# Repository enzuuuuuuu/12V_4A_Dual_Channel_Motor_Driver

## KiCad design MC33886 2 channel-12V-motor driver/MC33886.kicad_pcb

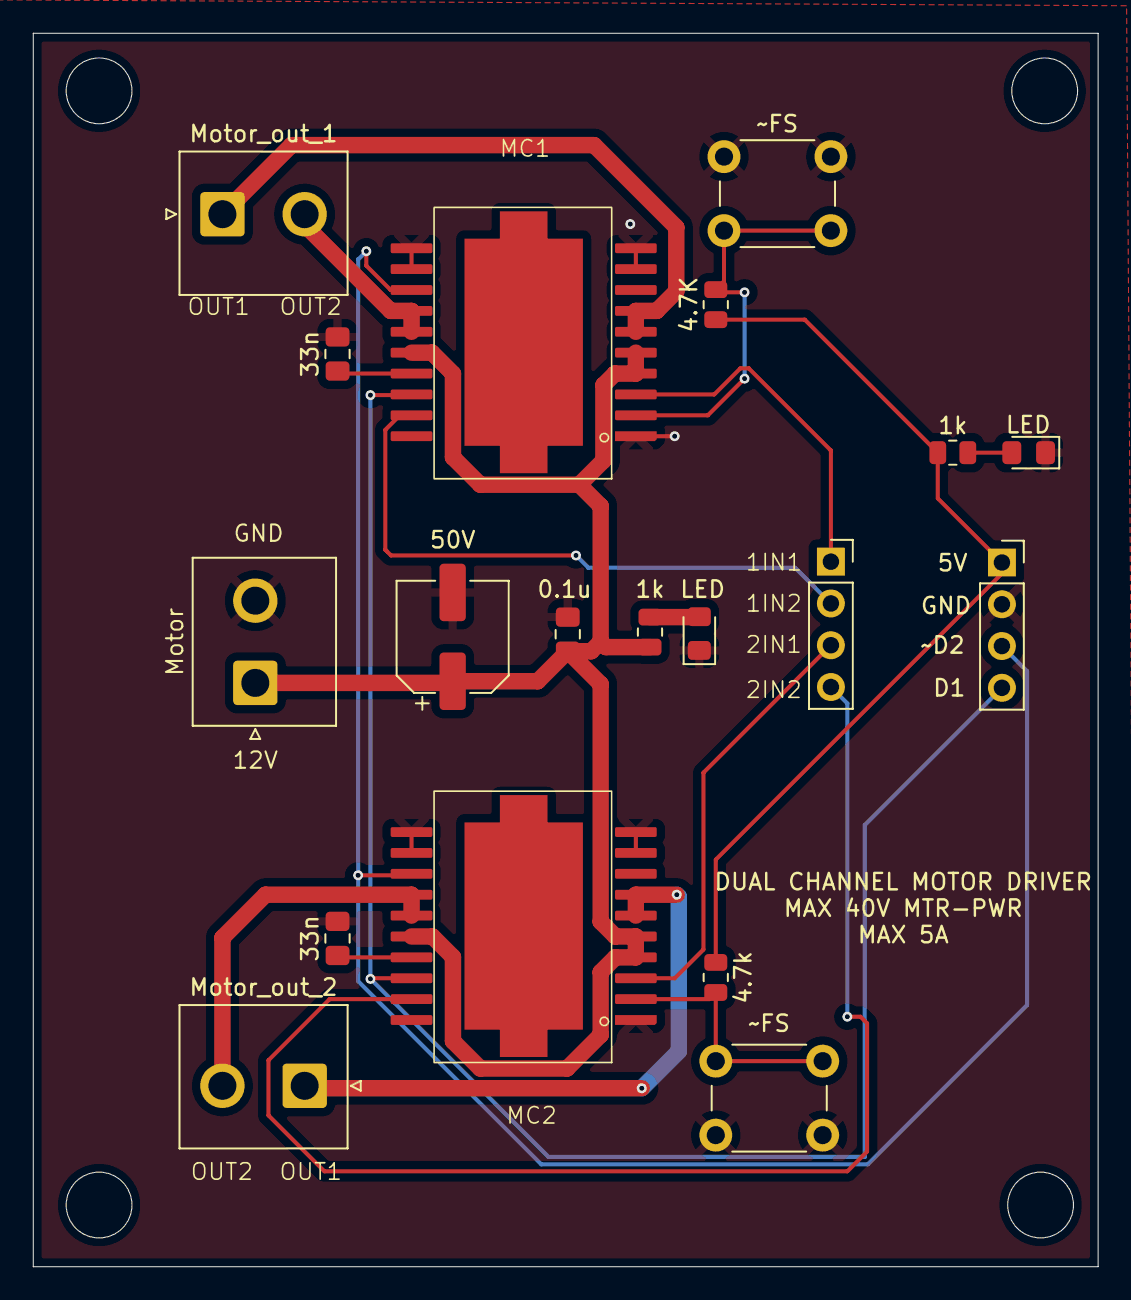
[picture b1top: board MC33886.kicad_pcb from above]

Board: 2 copper layers, 64.8 x 75.0 mm, 17 parts (0 on the bottom side), 19 nets.

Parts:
0.1u: 0.1u; C_0805_2012Metric_Pad1.18x1.45mm_HandSolder
1k, 1k#2: 1k; R_0805_2012Metric
4.7K, 4.7k: 4.7k; R_0805_2012Metric
33n, 33n#2: 33n; C_0805_2012Metric_Pad1.18x1.45mm_HandSolder
50V: 50V; CP_Elec_6.3x7.7
J2, J3: Conn_01x04_Pin; PinSocket_1x04_P2.54mm_Vertical
LED: LED; LED_0805_2012Metric_Pad1.15x1.40mm_HandSolder
LED#2: LED; LED_0805_2012Metric_Pad1.15x1.40mm_HandSolder
MC1, MC2: MC33886
Motor: Conn_01x02_Pin; JST_NV_B02P-NV_1x02_P5.00mm_Vertical
Motor_out_1, Motor_out_2: Conn_01x02_Pin; JST_NV_B02P-NV_1x02_P5.00mm_Vertical

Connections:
+5V: 1k.1, 4.7K.1, 4.7k.1, J3.1
+12V: 0.1u.1, 1k#2.1, 50V.1, MC1.4 (V+), MC1.5 (V+), MC1.16 (V+), MC2.4 (V+), MC2.5 (V+), MC2.16 (V+), Motor.1
GND: 0.1u.2, 33n.2, 33n#2.2, 50V.2, J3.2, LED.1 (K), LED#2.1 (K), MC1.1 (AGND), MC1.9 (PGND), MC1.10 (PGND), MC1.11 (PGND), MC1.12 (PGND), MC2.1 (AGND), MC2.9 (PGND), MC2.10 (PGND), MC2.11 (PGND), MC2.12 (PGND), Motor.2
unnamed: 1k.2, LED#2.2 (A)
unnamed: 1k#2.2, LED.2 (A)
unnamed: MC1.6 (OUT1), MC1.7 (OUT1), Motor_out_1.1
unnamed: MC1.14 (OUT2), MC1.15 (OUT2), Motor_out_1.2
unnamed: J2.1, MC1.3 (IN1)
unnamed: J2.2, MC1.19 (IN2)
unnamed: J2.3, MC2.3 (IN1)
unnamed: J2.4, MC2.19 (IN2)
unnamed: J3.3, MC1.13 (~D2), MC2.13 (~D2)
unnamed: J3.4, MC1.18 (D1), MC2.18 (D1)
unnamed: MC2.6 (OUT1), MC2.7 (OUT1), Motor_out_2.1
unnamed: MC2.14 (OUT2), MC2.15 (OUT2), Motor_out_2.2
unnamed: 33n#2.1, MC1.17 (CCP)
unnamed: 4.7K.2, MC1.2 (~FS)
unnamed: 33n.1, MC2.17 (CCP)
unnamed: 4.7k.2, MC2.2 (~FS)
